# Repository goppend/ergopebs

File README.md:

# ergopebs
A split-design ortholinear mechanical keyboard.

## Todo
- [x] Port what I have to KiCad.
- [x] Fix existing problems.
- [x] Consider design changes, add last minute features, ERC.
- [x] Ensure layout is sound. DRC.
- [ ] Finish v1 firmware to ensure layout is worth pursuing.
- [ ] Have v2 boards fabbed.
- [ ] (Awaiting boards/parts) Write firmware.
- [ ] Done!

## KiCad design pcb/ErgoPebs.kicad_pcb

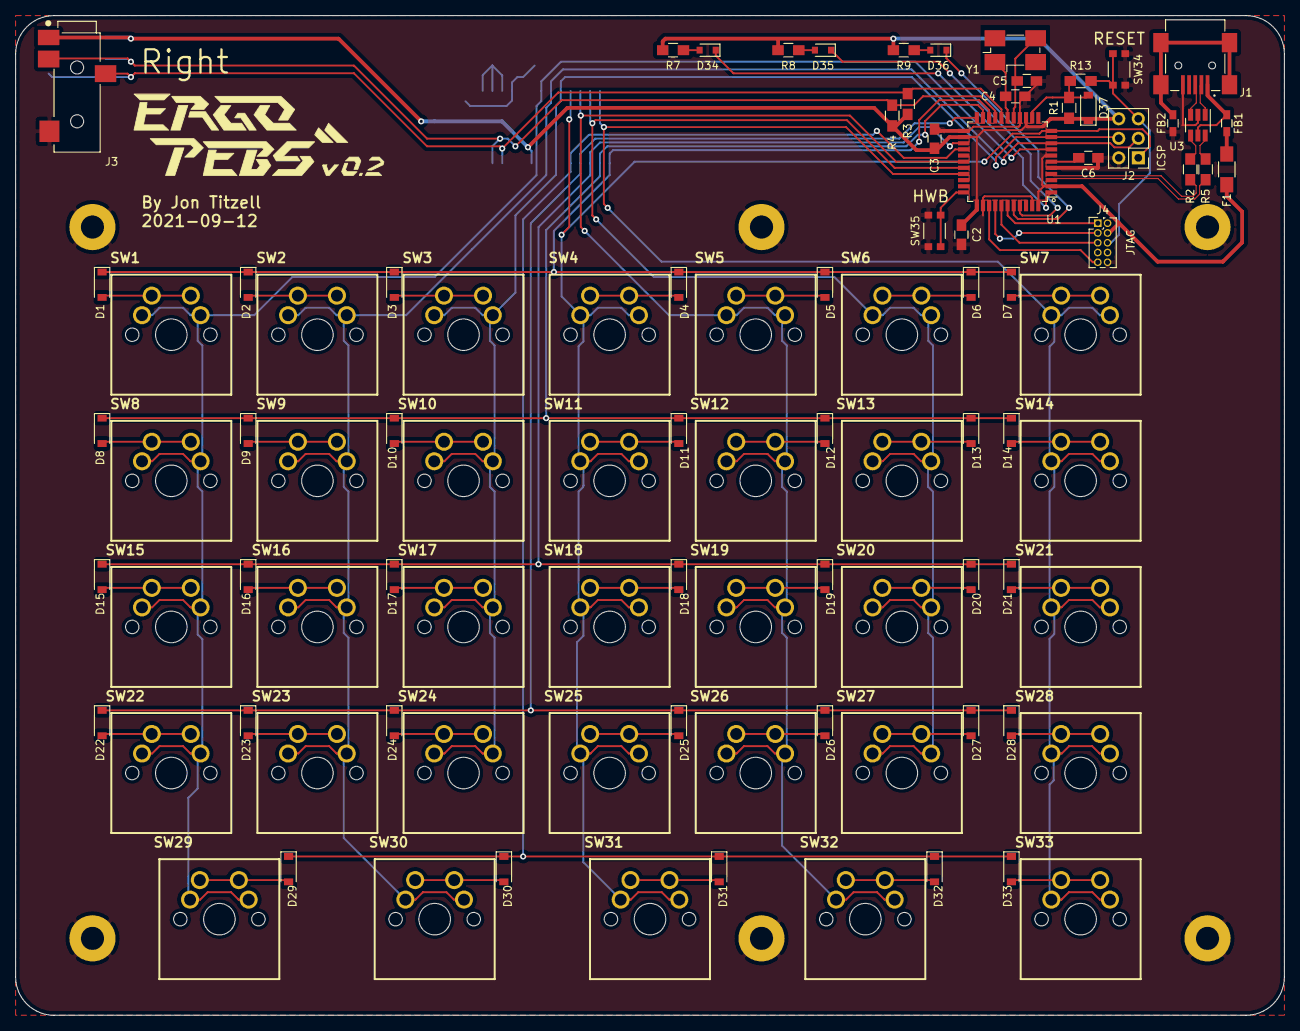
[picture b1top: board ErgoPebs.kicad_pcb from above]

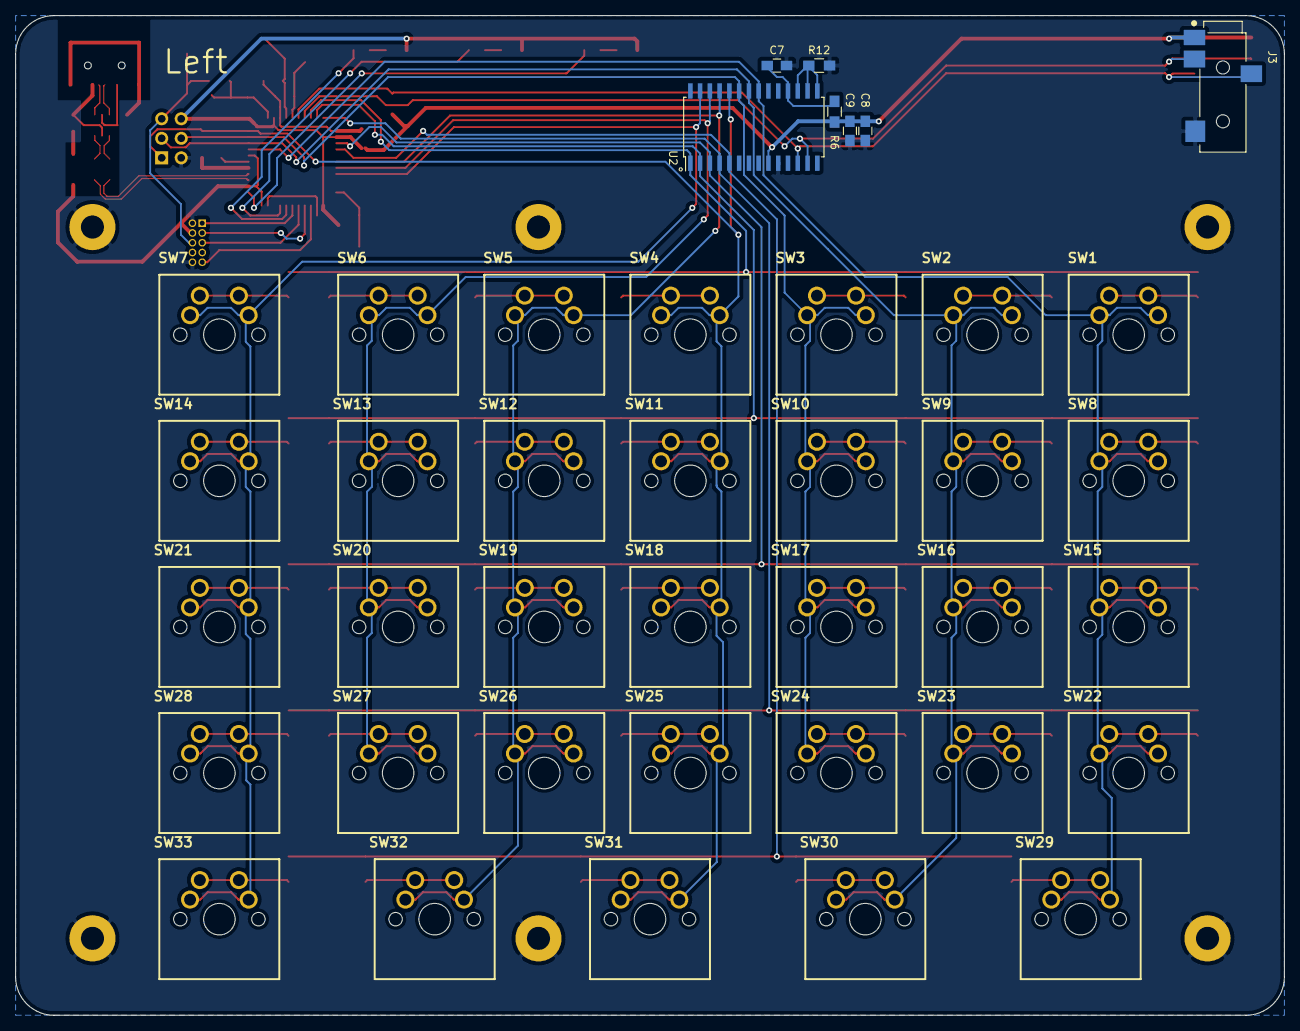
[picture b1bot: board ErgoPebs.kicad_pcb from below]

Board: 2 copper layers, 165.0 x 130.0 mm, 108 parts (6 on the bottom side), 76 nets.

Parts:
C2, C8: 10 uF; C_0805_HandSoldering
C3, C7, C9: 0.1 uF; C_0805_HandSoldering
C4, C5: 18 pF; C_0805_HandSoldering
C6: 1 uF; C_0805_HandSoldering
D1, D2, D3, D4, D5, D6, D7, D8, D9, D10, D11, D12, D13, D14, D15, D16, D17, D18, D19, D20, D21, D22, D23, D24, D25, D26, D27, D28, D29, D30, D31, D32, D33: 1N4148; D_SOD-123
D34: Num; D_0805
D35: Caps; D_0805
D36: Scroll; D_0805
D37: Schottky; D_SOD-123
F1: 500mA; R_1206_HandSoldering
FB1: BK1608HW121-T; R_0603_HandSoldering
FB2: BK1608HS330-T; R_0603_HandSoldering
H1, H2, H3, H4, H5, H6: MountingHole_Pad; MountingHole_3mm_Pad
J1: USB_B_Mini; CUI_UJ2-MBH-2-SMT
J2: AVR ISP; Pin_Header_Straight_2x03_Pitch2.54mm
J3: SJ-43514-SMT; CUI_SJ-43514-SMT-dual
J4: AVR JTAG; Pin_Header_Straight_2x05_Pitch1.27mm
R1, R6, R7, R8, R9: 1k; R_0805_HandSoldering
R2, R5: 22; R_0805_HandSoldering
R3, R4: 4.7k; R_0805_HandSoldering
R12, R13: 330; R_0805_HandSoldering
SW1, SW2, SW3, SW4, SW5, SW6, SW7, SW8, SW9, SW10, SW11, SW12, SW13, SW14, SW15, SW16, SW17, SW18, SW19, SW20, SW21, SW22, SW23, SW24, SW25, SW26, SW27, SW28, SW29, SW30, SW31, SW32, SW33: SW_SPST; MX1A-C1NW-dual
SW34, SW35: KMR621NGLFS
U1: ATmega32U4; TQFP-44_10x10mm_Pitch0.8mm
U2: MCP23017_SO; SOIC-28W_7.5x17.9mm_Pitch1.27mm
U3: USBLC6-2SC6; SOT-23-6_Handsoldering
Y1: 16 MHz; Crystal_SMD_0603-4pin_6.0x3.5mm_HandSoldering

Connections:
+5V: C2.1, C3.1, C8.1, C9.1, D37.1, F1.1, J2.6, J3.1, J4.4, R1.1, R3.1, R4.1, R6.1, R7.1, R8.1, R9.1, U1.2, U1.7, U1.14, U1.24, U1.34, U1.44, U2.9
/COL_1: SW1.1, SW8.1, SW15.1, SW22.1, SW29.1, U1.8, U2.21
/COL_2: J2.3, SW2.1, SW9.1, SW16.1, SW23.1, SW30.1, U1.9, U2.22
/COL_3: J2.4, SW3.1, SW10.1, SW17.1, SW24.1, U1.10, U2.23
/COL_4: J2.1, SW4.1, SW11.1, SW18.1, SW25.1, SW31.1, U1.11, U2.24
/COL_5: SW5.1, SW12.1, SW19.1, SW26.1, SW32.1, U1.28, U2.25
/COL_6: SW6.1, SW13.1, SW20.1, SW27.1, U1.29, U2.26
/COL_7: SW7.1, SW14.1, SW21.1, SW28.1, SW33.1, U1.30, U2.27
/D+: R2.1, U1.4
/D-: R5.1, U1.3
/ROW_1: D1.1, D2.1, D3.1, D4.1, D5.1, D6.1, D7.1, U1.20, U2.1
/ROW_2: D8.1, D9.1, D10.1, D11.1, D12.1, D13.1, D14.1, U1.21, U2.2
/ROW_3: D15.1, D16.1, D17.1, D18.1, D19.1, D20.1, D21.1, U1.25, U2.3
/ROW_4: D22.1, D23.1, D24.1, D25.1, D26.1, D27.1, D28.1, U1.22, U2.4
/ROW_5: D29.1, D30.1, D31.1, D32.1, D33.1, U1.26, U2.5
/SCL: J3.3, R3.2, U1.18, U2.12
/SDA: J3.4, R4.2, U1.19, U2.13
/UCAP: C6.1, U1.6
/_RESET: J2.5, J4.6, R13.1, SW34.2
GND: C2.2, C3.2, C4.2, C5.2, C6.2, C7.2, C8.2, C9.2, FB2.2, H1.1, H2.1, H3.1, H4.1, H5.1, H6.1, J1.5, J2.2, J3.2, J4.2, J4.10, R12.2, SW34.1, SW35.2, U1.5, U1.15, U1.23, U1.35, U1.43, U2.10, U3.2
unnamed: C4.1, U1.17, Y1.1
unnamed: C5.1, U1.16, Y1.3
unnamed: C7.1, R6.2, U2.18
unnamed: D1.2, SW1.2
unnamed: D2.2, SW2.2
unnamed: D3.2, SW3.2
unnamed: D4.2, SW4.2
unnamed: D5.2, SW5.2
unnamed: D6.2, SW6.2
unnamed: D7.2, SW7.2
unnamed: D8.2, SW8.2
unnamed: D9.2, SW9.2
unnamed: D10.2, SW10.2
unnamed: D11.2, SW11.2
unnamed: D12.2, SW12.2
unnamed: D13.2, SW13.2
unnamed: D14.2, SW14.2
unnamed: D15.2, SW15.2
unnamed: D16.2, SW16.2
unnamed: D17.2, SW17.2
unnamed: D18.2, SW18.2
unnamed: D19.2, SW19.2
unnamed: D20.2, SW20.2
unnamed: D21.2, SW21.2
unnamed: D22.2, SW22.2
unnamed: D23.2, SW23.2
unnamed: D24.2, SW24.2
unnamed: D25.2, SW25.2
unnamed: D26.2, SW26.2
unnamed: D27.2, SW27.2
unnamed: D28.2, SW28.2
unnamed: D29.2, SW29.2
unnamed: D30.2, SW30.2
unnamed: D31.2, SW31.2
unnamed: D32.2, SW32.2
unnamed: D33.2, SW33.2
unnamed: D34.1, U1.1
unnamed: D34.2, R7.2
unnamed: D35.1, U1.41
unnamed: D35.2, R8.2
unnamed: D36.1, U1.40
unnamed: D36.2, R9.2
unnamed: D37.2, R1.2, R13.2, U1.13
unnamed: F1.2, FB1.1
unnamed: FB1.2, J1.1, U3.5
unnamed: FB2.1, J1.6
unnamed: J1.2, U3.1
unnamed: J1.3, U3.3
unnamed: J4.1, U1.39
unnamed: J4.3, U1.37
unnamed: J4.5, U1.38
unnamed: J4.9, U1.36
unnamed: R2.2, U3.4
unnamed: R5.2, U3.6
unnamed: R12.1, U2.15, U2.16, U2.17
unnamed: SW35.1, U1.33

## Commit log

2022-03-05 V1, the old designspark project.
2022-03-05 Initial v2 pcb commit.
